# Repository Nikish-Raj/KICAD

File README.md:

# KICAD
files for E1-E4 are in exp folder

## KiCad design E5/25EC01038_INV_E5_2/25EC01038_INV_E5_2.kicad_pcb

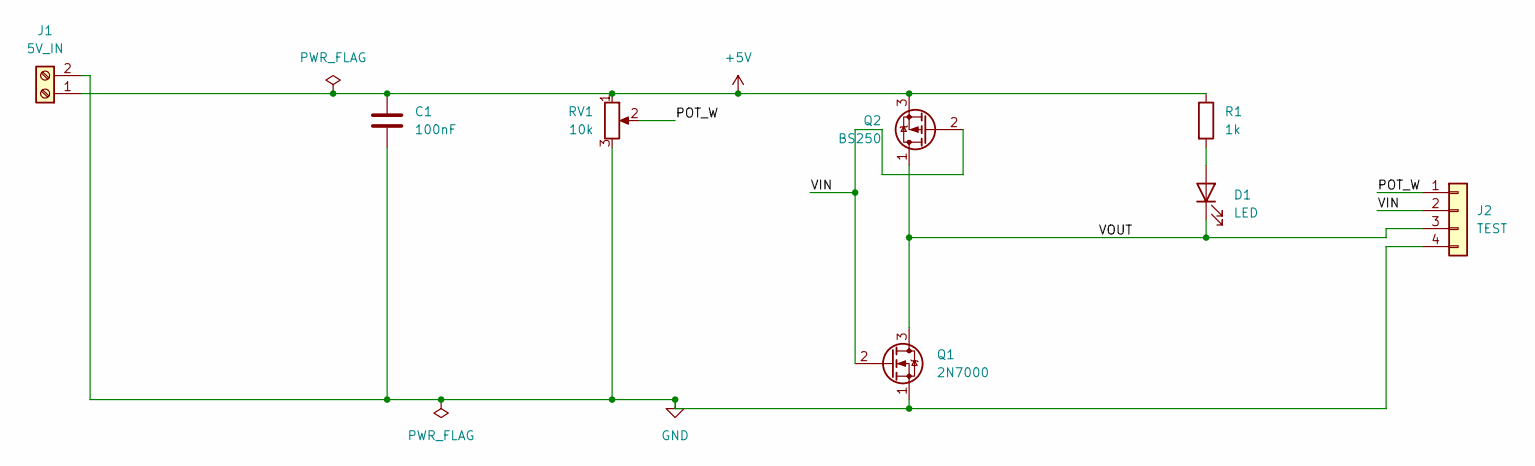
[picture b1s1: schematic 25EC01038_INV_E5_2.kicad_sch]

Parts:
C1: 100nF; C_Disc_D5.0mm_W2.5mm_P5.00mm
D1: LED; LED_D3.0mm
J1: 5V_IN; TerminalBlock_Phoenix_MKDS-1,5-2-5.08_1x02_P5.08mm_Horizont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
J2: TEST; PinHeader_1x04_P2.54mm_Vertical
Q1: 2N7000; TO-92_Inline
Q2: BS250; TO-92_Inline
R1: 1k; R_Axial_DIN0207_L6.3mm_D2.5mm_P10.16mm_Horizontal
RV1: 10k; Potentiometer_Bourns_3386P_Vertical

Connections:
+5V: C1.1, J1.1, Q2.3 (S), R1.1, RV1.1
/POT_W: J2.1, RV1.2
/VIN: J2.2, Q1.2 (G), Q2.2 (G)
/VOUT: D1.1 (K), J2.3, Q1.3 (D), Q2.1 (D)
GND: C1.2, J1.2, J2.4, Q1.1 (S), RV1.3
unnamed: D1.2 (A), R1.2

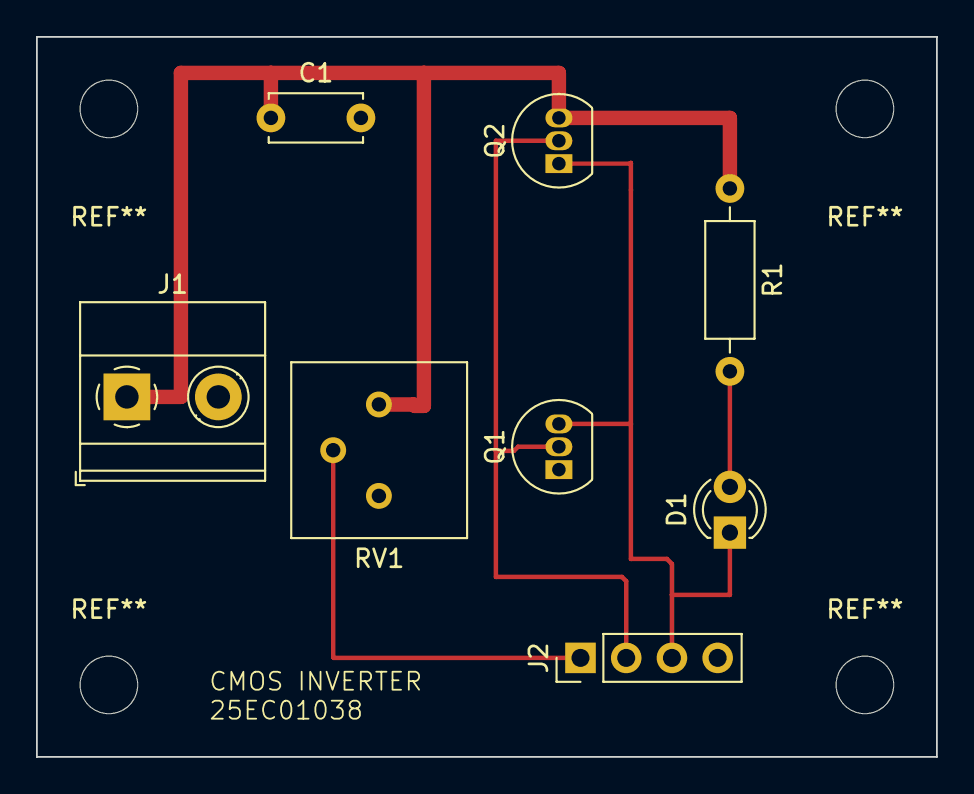
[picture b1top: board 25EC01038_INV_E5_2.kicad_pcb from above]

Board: 2 copper layers, 50.0 x 40.0 mm, 8 parts (0 on the bottom side), 6 nets.
